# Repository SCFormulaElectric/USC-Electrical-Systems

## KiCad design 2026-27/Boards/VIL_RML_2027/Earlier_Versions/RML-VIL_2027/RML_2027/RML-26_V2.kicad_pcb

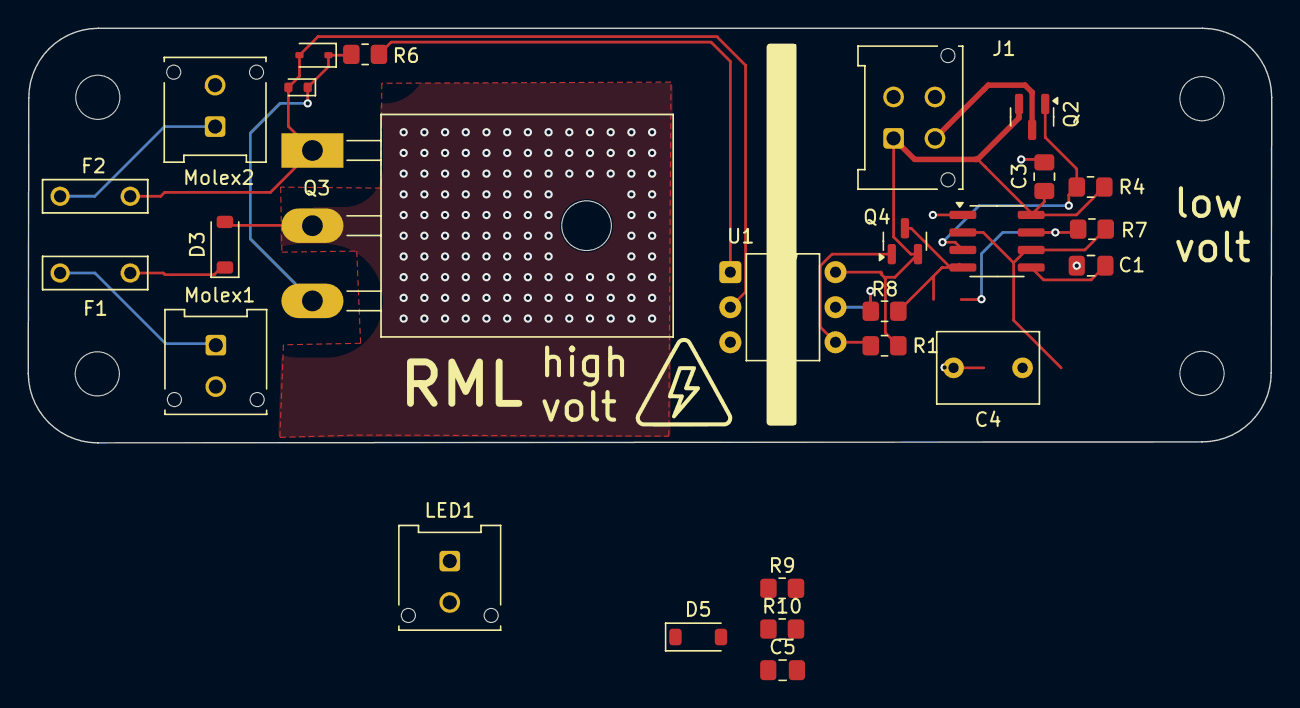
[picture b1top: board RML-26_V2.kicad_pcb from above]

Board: 2 copper layers, 90.1 x 30.0 mm, 30 parts (0 on the bottom side), 17 nets.

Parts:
C1: 0.1uF; C_0805_2012Metric_Pad1.18x1.45mm_HandSolder
C3: 1uF; C_0805_2012Metric_Pad1.18x1.45mm_HandSolder
C4: 1uF film; C_Rect_L7.2mm_W5.0mm_P5.00mm
C5: 100nF; C_0805_2012Metric_Pad1.18x1.45mm_HandSolder
D1: 1N4148WT-7; D_SOD-523
D3: BZT52C51-7-F; D_SOD-123
D4: PESD12VL1BA; D_SOD-323
D5: BZT52C8V2; D_SOD-123
F1, F2: 750mA; FUSE_BK_PCS
H1, H2, H3, H4: MountingHole; MountingHole_3.2mm_M3
J1: 043045-0412; Molex_Micro-Fit_3.0_43045-0412_2x02_P3.00mm_Vertical
LED1: 043045-0212; Molex_Micro-Fit_3.0_43045-0212_2x01_P3.00mm_Vertical
Molex1, Molex2: 043045-0212; Molex_Micro-Fit_3.0_43045-0212_2x01_P3.00mm_Vertical
Q2: AO3400A; SOT-23
Q3: UJ3N065080K3S; TO-247-3_Horizontal_TabDown
Q4: AO3401A; SOT-23
R1: 2k; R_0805_2012Metric_Pad1.20x1.40mm_HandSolder
R4: 100k; R_0805_2012Metric_Pad1.20x1.40mm_HandSolder
R6: 5.6k; R_0805_2012Metric_Pad1.20x1.40mm_HandSolder
R7: 750k; R_0805_2012Metric_Pad1.20x1.40mm_HandSolder
R8, R10: 1k; R_0805_2012Metric_Pad1.20x1.40mm_HandSolder
R9: 10k; R_0805_2012Metric_Pad1.20x1.40mm_HandSolder
U1: H11L1; DIP-6_W7.62mm
U2: LMC555CMX/NOPB; SOIC-8_3.9x4.9mm_P1.27mm

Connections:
/HV+: F1.1, Molex1.1, Molex1.2
/HV-: D1.2 (A), D4.2 (A2), F2.1, LED1.1, Q3.1 (G), U1.2
GLV+: C3.2, C5.2, J1.1, Q4.2 (S), R1.1, R9.2, U1.6, U2.8 (VCC)
GND: C1.1, C3.1, C4.2, C5.1, D5.2 (A), J1.2, Q2.2 (S), R4.1, R8.1, U1.5, U2.1 (GND)
LED_RETURN: J1.3, Q2.3 (D)
unnamed: D1.1 (K), D4.1 (A1), Q3.3 (S), R6.1, R10.1
unnamed: D3.2 (A), Q3.2 (D)
unnamed: D3.1 (K), F1.2
unnamed: D5.1 (K), Q2.1 (G), R4.2, R9.1, U2.7 (DIS)
unnamed: LED1.2, R10.2
unnamed: F2.2, Molex2.1, Molex2.2
unnamed: Q4.3 (D), R8.2, U2.4 (R)
unnamed: Q4.1 (G), R1.2, U1.4
unnamed: R6.2, U1.1
unnamed: C1.2, U2.5 (CV)
unnamed: R7.2, U2.3 (Q)
unnamed: C4.1, R7.1, U2.2 (TR), U2.6 (THR)

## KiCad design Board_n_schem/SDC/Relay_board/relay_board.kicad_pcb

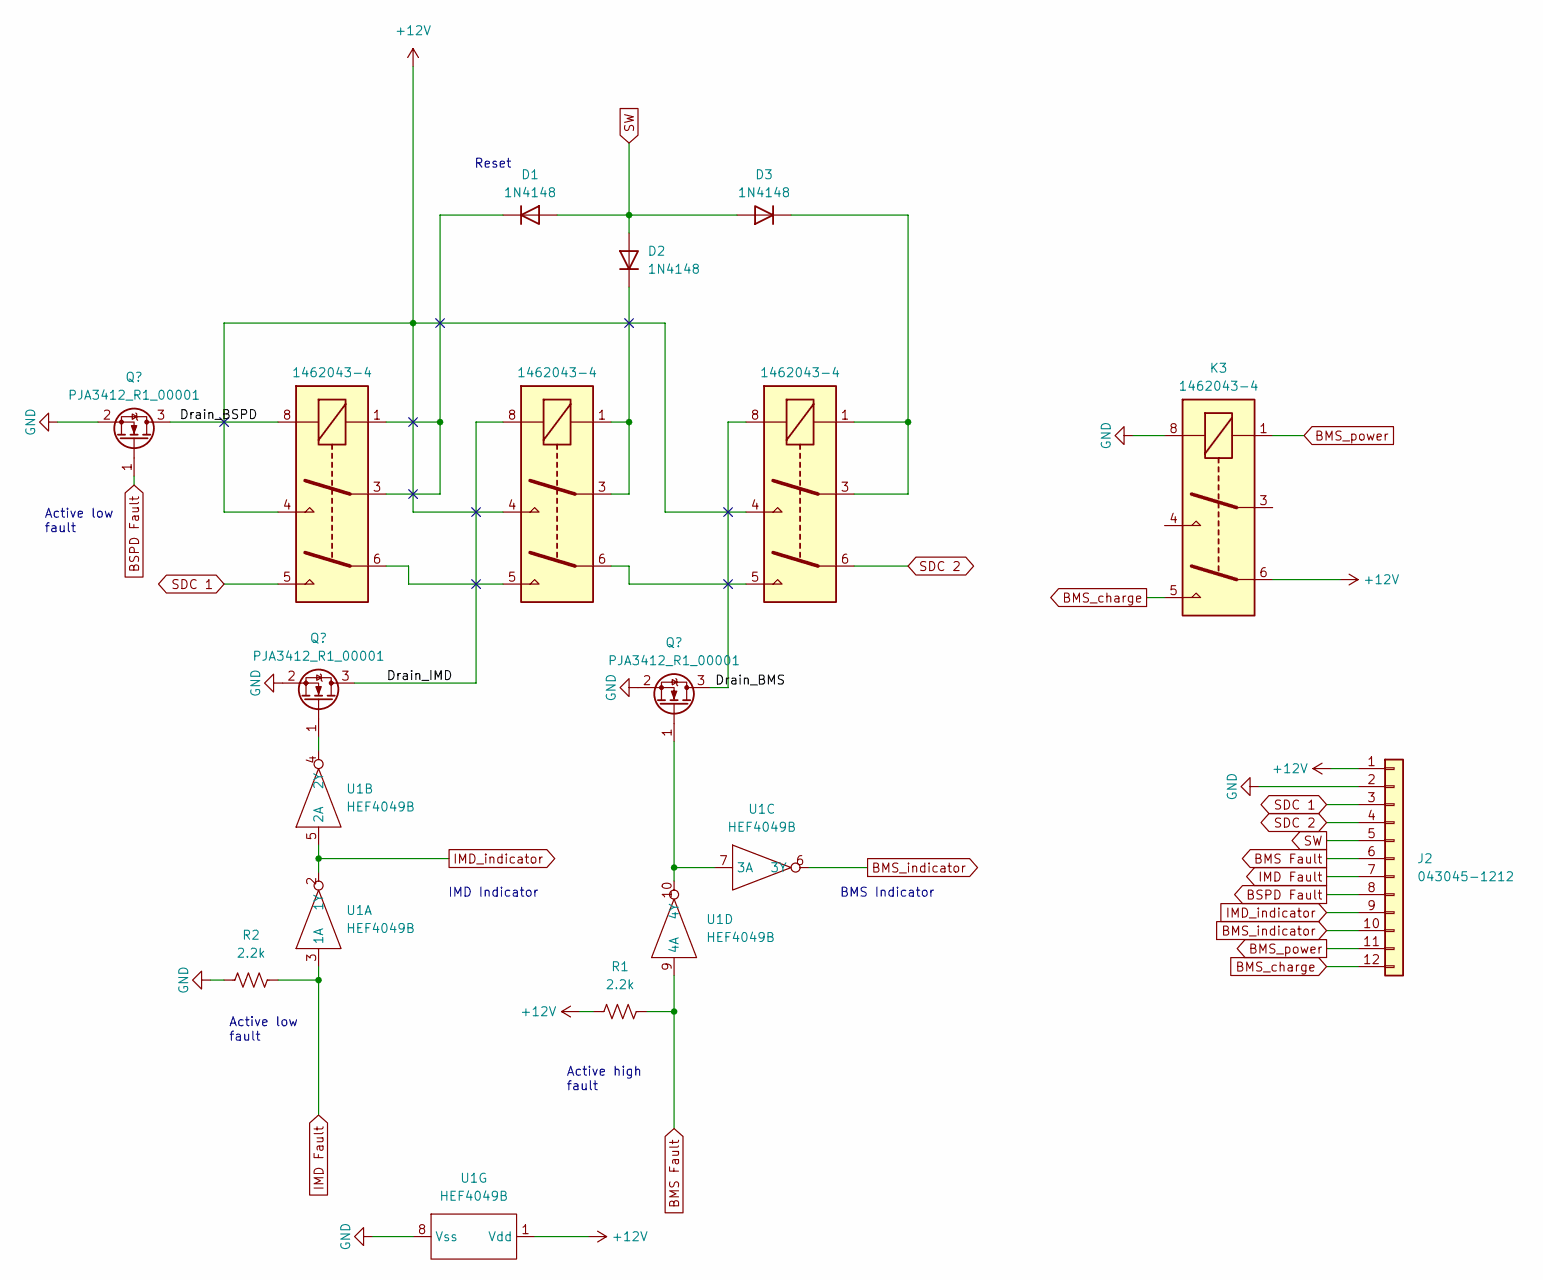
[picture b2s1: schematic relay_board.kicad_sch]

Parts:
D1, D2, D3: 1N4148; D_DO-35_SOD27_P7.62mm_Horizontal
J2: 043045-1212; Molex_Micro-Fit_3.0_43045-1212_2x06_P3.00mm_Vertical
K1, K2, K3, K4: 1462043-4; Relay_DPDT_AXICOM_IMSeries_JLeg
Q1, Q2, Q3: PJA3412_R1_00001; SOT-23
R1, R2: 2.2k; R_Axial_DIN0207_L6.3mm_D2.5mm_P7.62mm_Horizontal
U1: HEF4049B; SO-16_3.9x9.9mm_P1.27mm

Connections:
+12V: J2.1, K1.4, K2.4, K3.6, K4.4, R1.2, U1.1 (Vdd)
BMS Fault: J2.6, R1.1, U1.9 (4A)
BMS_charge: J2.12, K3.5
BMS_indicator: J2.10, U1.6 (3Y)
BMS_power: J2.11, K3.1
BSPD Fault: J2.8, Q1.1 (G)
IMD Fault: J2.7, R2.1, U1.3 (1A)
IMD_indicator: J2.9, U1.2 (1Y), U1.5 (2A)
unnamed: D1.1 (K), K4.1, K4.3
unnamed: D2.1 (K), K1.1, K1.3
unnamed: D3.1 (K), K2.1, K2.3
unnamed: K1.5, K4.6
unnamed: K1.6, K2.5
unnamed: Q2.1 (G), U1.4 (2Y)
unnamed: Q3.1 (G), U1.7 (3A), U1.10 (4Y)
SDC 1: J2.3, K4.5
SDC 2: J2.4, K2.6
SW: D1.2 (A), D2.2 (A), D3.2 (A), J2.5

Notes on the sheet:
Active low fault
Active high fault
Reset
Active low fault
IMD Indicator
BMS Indicator

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
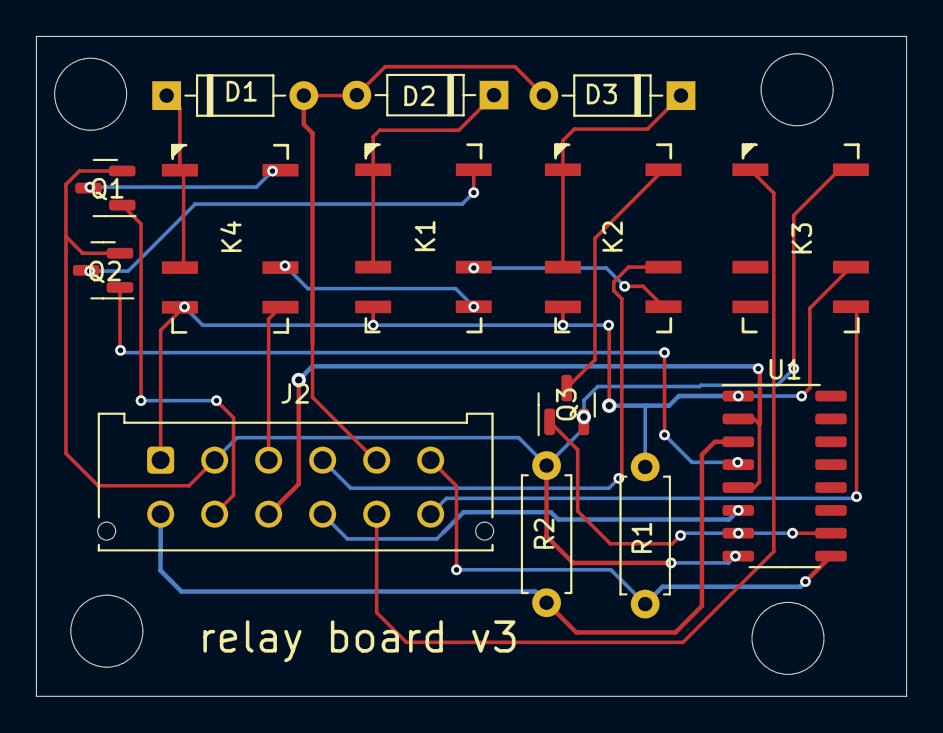
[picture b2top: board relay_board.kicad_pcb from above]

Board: 2 copper layers, 48.3 x 36.7 mm, 14 parts (0 on the bottom side), 22 nets.

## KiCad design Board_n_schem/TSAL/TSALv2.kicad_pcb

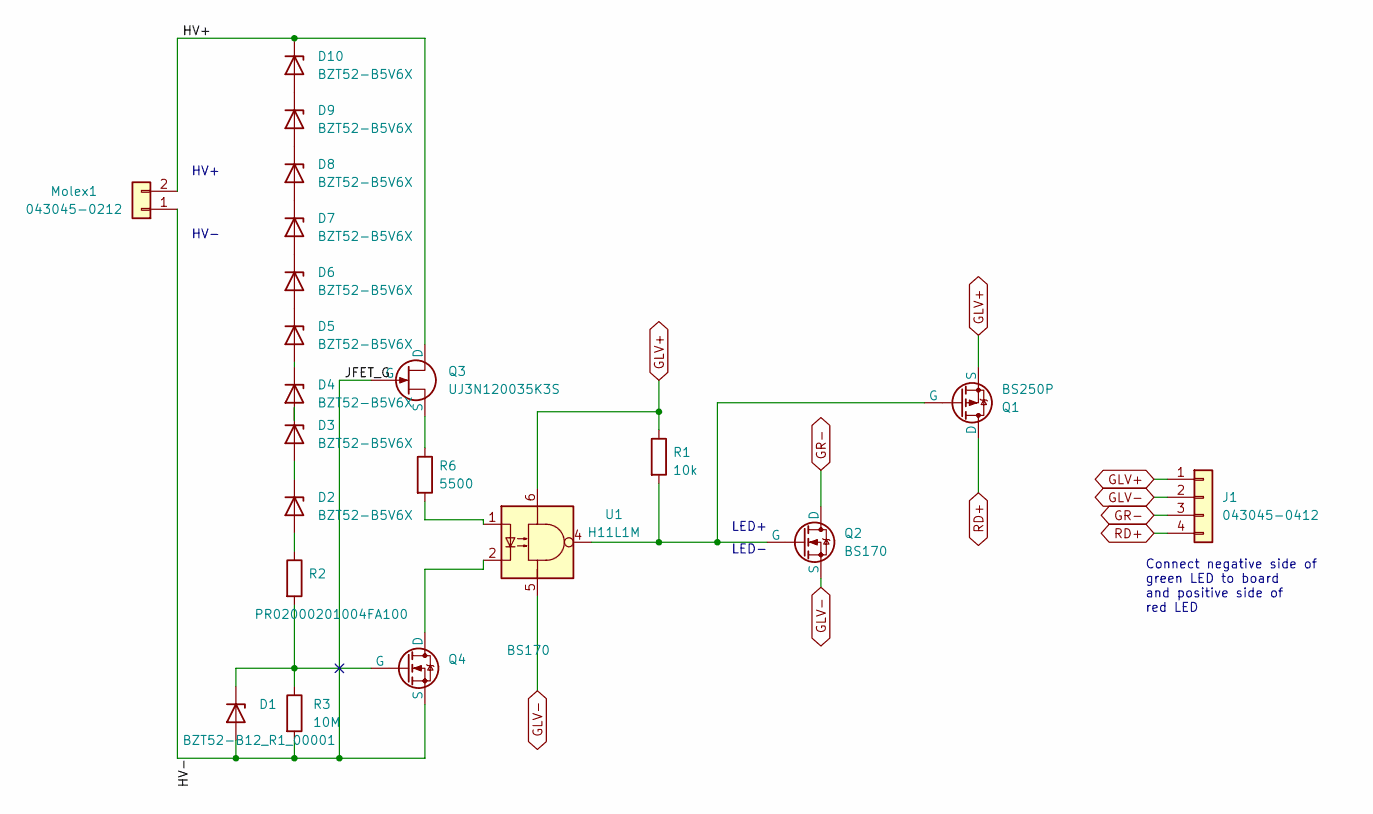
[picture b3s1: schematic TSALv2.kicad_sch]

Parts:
D1: BZT52-B12_R1_00001; D_SOD-123
D2, D3, D4, D5, D6, D7, D8, D9, D10: BZT52-B5V6X; D_SOD-123
J1: 043045-0412; Molex_Micro-Fit_3.0_43045-0412_2x02_P3.00mm_Vertical
Molex1: 043045-0212; Molex_Micro-Fit_3.0_43045-0212_2x01_P3.00mm_Vertical
Q1: BS250P; TO-92
Q2, Q4: BS170; TO-92
Q3: UJ3N120035K3S; TO-247-3_Horizontal_TabDown
R1: 10k; R_Axial_DIN0207_L6.3mm_D2.5mm_P7.62mm_Horizontal
R2: PR02000201004FA100; R_Axial_DIN0207_L6.3mm_D2.5mm_P7.62mm_Horizontal
R3: 10M; R_Axial_DIN0207_L6.3mm_D2.5mm_P7.62mm_Horizontal
R6: 5500; R_Axial_DIN0207_L6.3mm_D2.5mm_P7.62mm_Horizontal
U1: H11L1M; DIP-6_W7.62mm

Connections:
GLV+: J1.1, Q1.3 (S), R1.1, U1.6
GLV-: J1.2, Q2.3 (S), U1.5
GR-: J1.3, Q2.1 (D)
unnamed: D1.2 (A), Molex1.1, Q3.1 (G), Q4.3 (S), R3.2
unnamed: D1.1 (K), Q4.2 (G), R2.2, R3.1
unnamed: D2.2 (A), R2.1
unnamed: D2.1 (K), D3.2 (A)
unnamed: D3.1 (K), D4.2 (A)
unnamed: D4.1 (K), D5.2 (A)
unnamed: D5.1 (K), D6.2 (A)
unnamed: D6.1 (K), D7.2 (A)
unnamed: D7.1 (K), D8.2 (A)
unnamed: D8.1 (K), D9.2 (A)
unnamed: D9.1 (K), D10.2 (A)
unnamed: D10.1 (K), Molex1.2, Q3.2 (D)
unnamed: Q1.2 (G), Q2.2 (G), R1.2, U1.4
unnamed: Q3.3 (S), R6.1
unnamed: Q4.1 (D), U1.2
unnamed: R6.2, U1.1
RD+: J1.4, Q1.1 (D)

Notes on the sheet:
Connect negative side of green LED to board and positive side of red LED
LED-
LED+
HV+
HV-

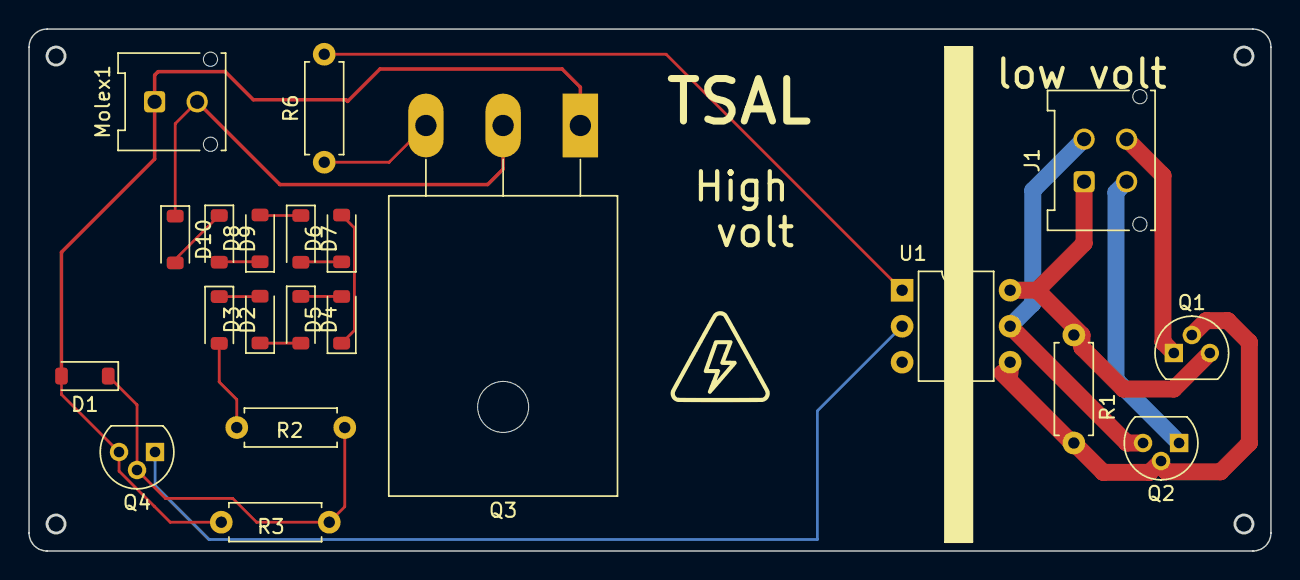
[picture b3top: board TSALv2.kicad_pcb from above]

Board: 2 copper layers, 87.6 x 36.8 mm, 21 parts (0 on the bottom side), 20 nets.

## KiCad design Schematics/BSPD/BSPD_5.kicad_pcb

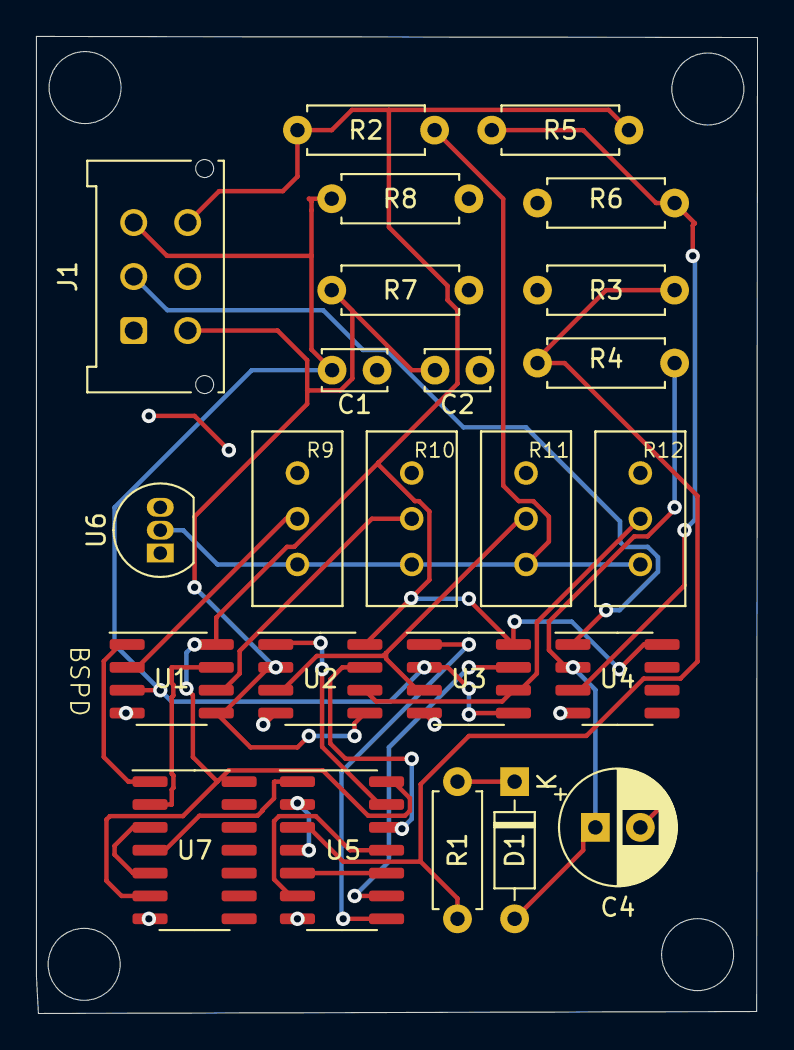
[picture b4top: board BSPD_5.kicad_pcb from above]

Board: 2 copper layers, 40.1 x 54.3 mm, 24 parts (0 on the bottom side), 25 nets.

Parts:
C1, C2: 0.1u; C_Disc_D3.4mm_W2.1mm_P2.50mm
C4: 12u; CP_Radial_D6.3mm_P2.50mm
D1: 1N4148; D_DO-35_SOD27_P7.62mm_Horizontal
J1: 043045-0612; Molex_Micro-Fit_3.0_43045-0612_2x03_P3.00mm_Vertical
R1: 1k; R_Axial_DIN0207_L6.3mm_D2.5mm_P7.62mm_Horizontal
R2: 2.7k; R_Axial_DIN0207_L6.3mm_D2.5mm_P7.62mm_Horizontal
R3: 5k; R_Axial_DIN0207_L6.3mm_D2.5mm_P7.62mm_Horizontal
R4: 50k; R_Axial_DIN0207_L6.3mm_D2.5mm_P7.62mm_Horizontal
R5, R6: 47k; R_Axial_DIN0207_L6.3mm_D2.5mm_P7.62mm_Horizontal
R7, R8: 10k; R_Axial_DIN0207_L6.3mm_D2.5mm_P7.62mm_Horizontal
R9, R10, R11, R12: T93YA103KT20; Potentiometer_Vishay_T93YA103KT20
U1, U2, U3, U4: LM358; SOIC-8_3.9x4.9mm_P1.27mm
U5: HEF4071B (OR); SOIC-14_3.9x8.7mm_P1.27mm
U6: LM4040LP-5; TO-92_Inline
U7: HEF4011B (NAND); SOIC-14_3.9x8.7mm_P1.27mm

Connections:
0.5V: R11.B, U2.3 (+), U3.3 (+)
4.5V: R12.B, U2.6 (-), U3.6 (-)
5V: R2.2, R9.C, R10.C, R11.C, R12.C, U6.2 (K)
12V: J1.6, R2.1, R5.2, U1.8 (V+), U2.8 (V+), U3.8 (V+), U4.8 (V+), U5.14 (VDD), U7.6 (2B), U7.14 (VDD)
BSPD_signal: J1.2, U4.1
GND: C1.2, C2.2, C4.2, J1.5, R3.1, R6.1, R7.2, R8.1, R9.A, R10.A, R11.A, R12.A, U1.4 (V-), U2.4 (V-), U3.4 (V-), U4.4 (V-), U5.7 (VSS), U6.3 (A), U7.7 (VSS)
unnamed: C4.1, D1.2 (A), R4.2, U4.2 (-)
unnamed: D1.1 (K), R1.2
unnamed: R9.B, U1.2 (-)
unnamed: R10.B, U1.6 (-)
unnamed: R5.1, R6.2, U4.3 (+)
unnamed: U5.2 (1B), U5.4 (2Y)
unnamed: U5.5 (2A), U5.10 (3Y)
unnamed: U5.6 (2B), U5.11 (4Y)
unnamed: U7.3 (1Y), U7.5 (2A)
brake: C2.1, J1.4, R7.1, U1.5 (+), U2.2 (-), U2.5 (+)
brake_short_ground: U2.1, U5.13 (4B)
brake_short_power: U2.7, U5.12 (4A)
current: C1.1, J1.3, R8.2, U1.3 (+), U3.2 (-), U3.5 (+)
current_short_ground: U3.1, U5.8 (3A)
current_short_power: U3.7, U5.9 (3B)
fault: R1.1, R3.2, R4.1, U5.3 (1Y)
fault_1: U5.1 (1A), U7.4 (2Y)
hard_brake: U1.7, U7.2 (1B)
high_current: U1.1, U7.1 (1A)

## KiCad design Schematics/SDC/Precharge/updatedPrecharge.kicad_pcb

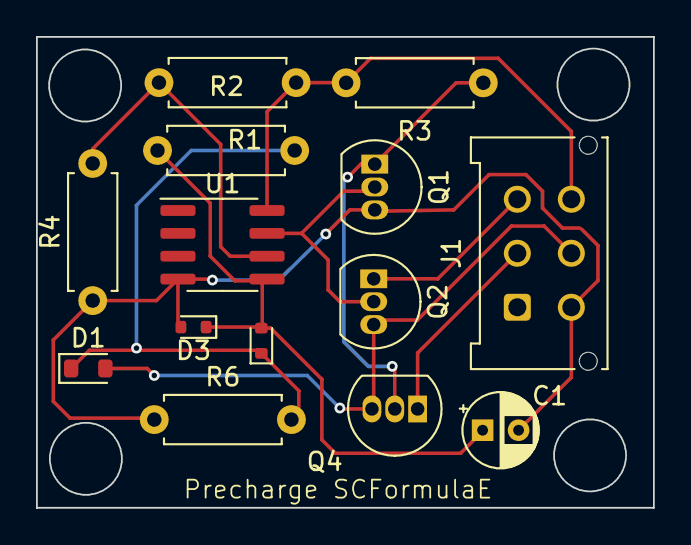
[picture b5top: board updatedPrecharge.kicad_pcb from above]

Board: 2 copper layers, 34.3 x 26.2 mm, 14 parts (0 on the bottom side), 10 nets.

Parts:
C1: 10uF; CP_Radial_D4.0mm_P2.00mm
D1: PD3S0230; D_SOD-110
D2, D3: 1N4148WTQ-7; D_SOD-523
J1: Conn_01x06; Molex_Micro-Fit_3.0_43045-0612_2x03_P3.00mm_Vertical
Q1: VN3205N3-G; TO-92_Inline
Q2, Q4: VP3203N3-G; TO-92_Inline
R1, R3, R4, R6: 10k; R_Axial_DIN0207_L6.3mm_D2.5mm_P7.62mm_Horizontal
R2: 1.8M; R_Axial_DIN0207_L6.3mm_D2.5mm_P7.62mm_Horizontal
U1: LM358DR2G; SOIC-8_3.9x4.9mm_P1.27mm

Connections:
/opamp_out: Q1.2 (G), Q2.2 (G), U1.7 (OUT_B)
/opamp_out_inv: Q1.1 (D), Q4.2 (G), R3.1
AIR+: J1.2, Q4.1 (D)
GND: C1.2, D3.2 (A), J1.4, Q1.3 (S), R4.1, R6.1, U1.4 (Vee/GND)
unnamed: D1.1 (K), D2.1 (K), R2.2, R6.2
unnamed: C1.1, D2.2 (A), D3.1 (K), R2.1, U1.5 (IN_B+)
unnamed: R1.2, R4.2, U1.6 (IN_B-)
PreAIR: J1.3, Q2.1 (D)
SDCin: D1.2 (A), J1.5, Q2.3 (S), Q4.3 (S)
Vcc: J1.6, R1.1, R3.2, U1.8 (VCC)

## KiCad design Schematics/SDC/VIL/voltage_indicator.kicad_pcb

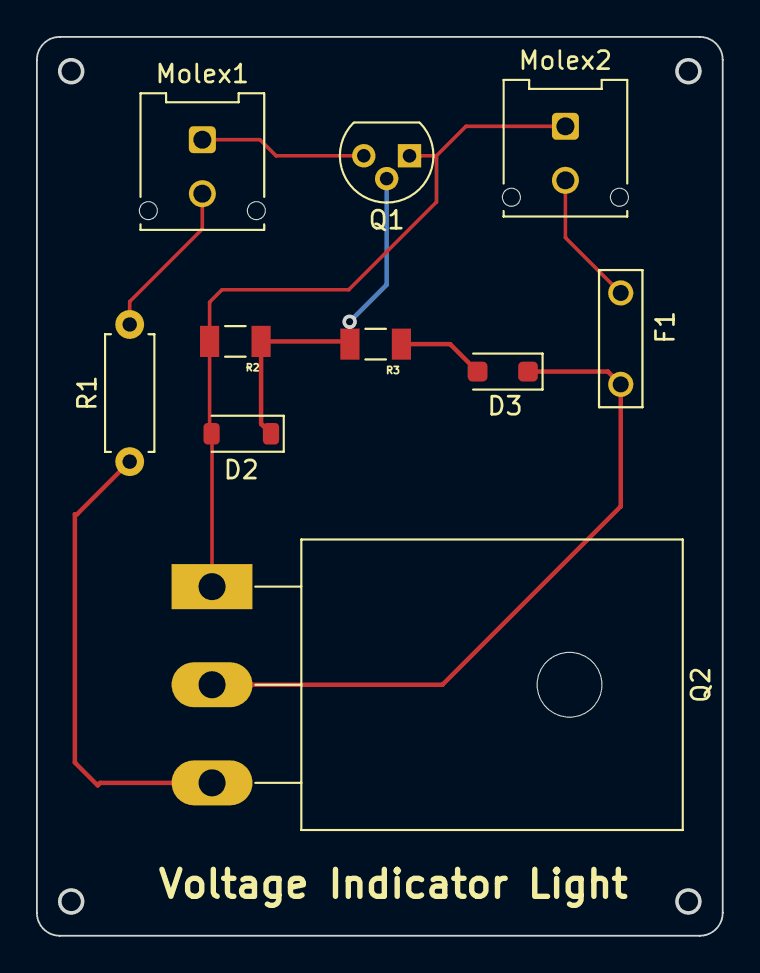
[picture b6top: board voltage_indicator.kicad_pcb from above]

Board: 2 copper layers, 38.1 x 49.9 mm, 10 parts (0 on the bottom side), 8 nets.

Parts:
D2: BZT52-B12_R1_00001; D_SOD-123
D3: PZ1AL62B-AU_R1_000A1; D_SOD-123F
F1: 750mA; FUSE_BK_PCS
Molex1, Molex2: 043045-0212; Molex_Micro-Fit_3.0_43045-0212_2x01_P3.00mm_Vertical
Q1: VN2460; TO-92
Q2: UJ3N120035K3S; TO-247-3_Horizontal_TabDown
R1: 1100; R_Axial_DIN0207_L6.3mm_D2.5mm_P7.62mm_Horizontal
R2, R3: RK73G2BTTD1004C; RESC3116X65N

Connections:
/HV+: F1.1, Molex2.2
/HV-: D2.2 (A), Molex2.1, Q1.1 (S), Q2.1 (G), R2.2
/LED+: Molex1.2, R1.2
/LED-: Molex1.1, Q1.3 (D)
unnamed: D2.1 (K), Q1.2 (G), R2.1, R3.2
unnamed: D3.2 (A), R3.1
unnamed: D3.1 (K), F1.2, Q2.2 (D)
unnamed: Q2.3 (S), R1.1
